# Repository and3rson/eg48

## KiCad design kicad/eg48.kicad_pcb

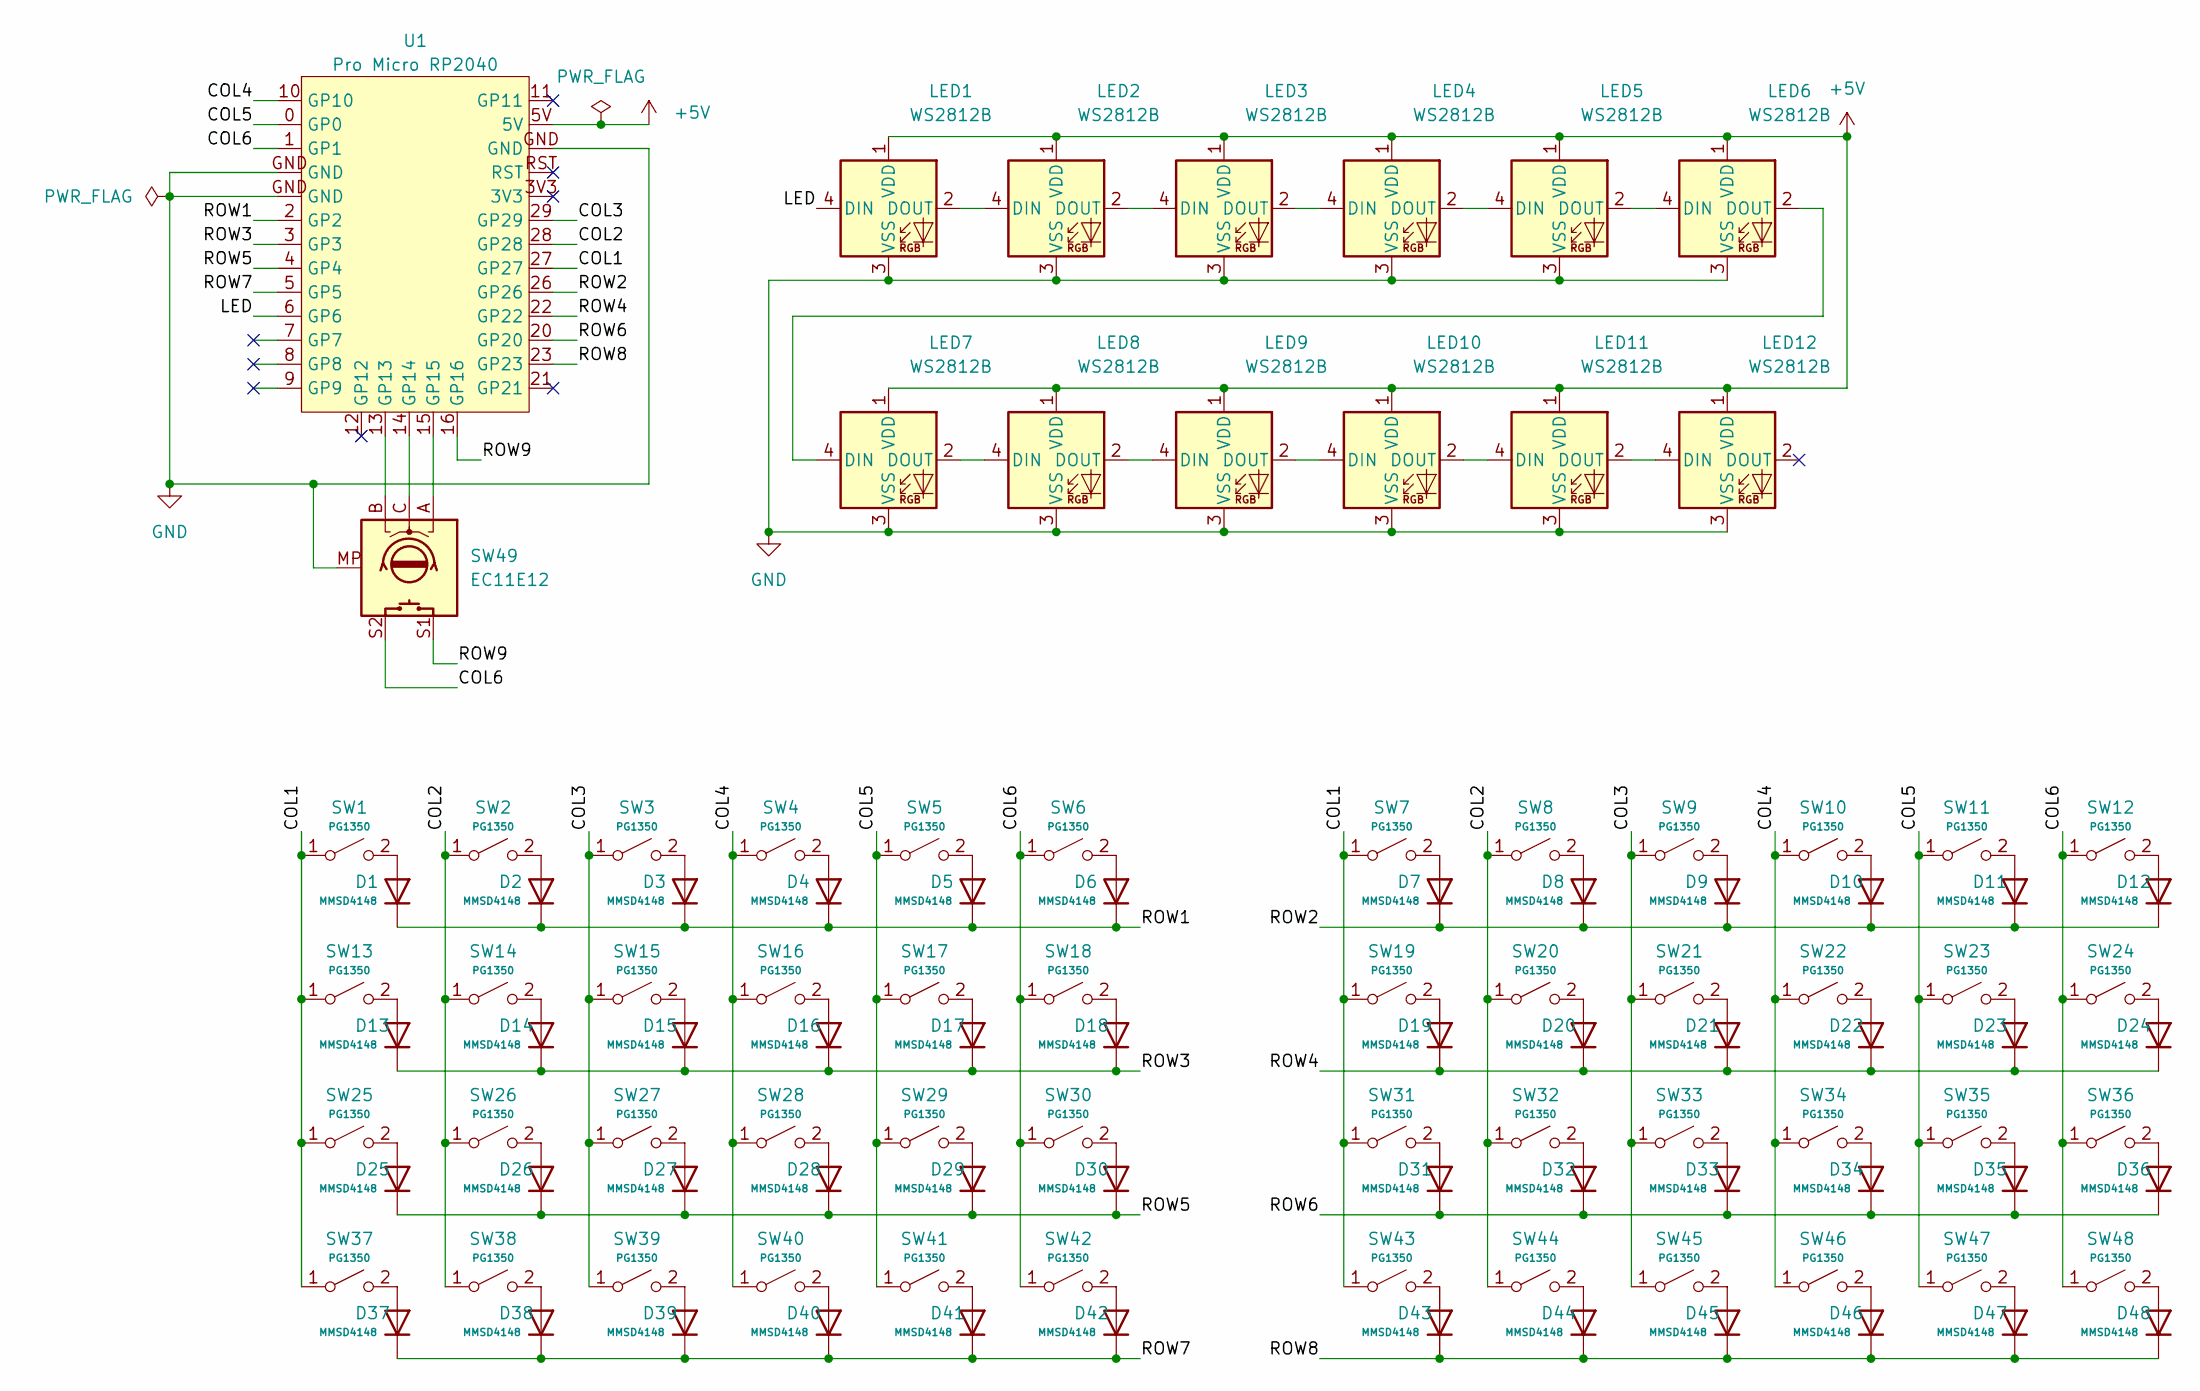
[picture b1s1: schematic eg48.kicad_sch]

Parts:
D1, D2, D3, D4, D5, D6, D7, D8, D9, D10, D11, D12, D13, D14, D15, D16, D17, D18, D19, D20, D21, D22, D23, D24, D25, D26, D27, D28, D29, D30, D31, D32, D33, D34, D35, D36, D37, D38, D39, D40, D41, D42, D43, D44, D45, D46, D47, D48: MMSD4148; D_SOD-123
LED1, LED2, LED3, LED4, LED5, LED6, LED7, LED8, LED9, LED10, LED11, LED12: WS2812B; LED_WS2812B_PLCC4_5.0x5.0mm_P3.2mm
SW1, SW2, SW3, SW4, SW5, SW6, SW7, SW8, SW9, SW10, SW11, SW12, SW13, SW14, SW15, SW16, SW17, SW18, SW19, SW20, SW21, SW22, SW23, SW24, SW25, SW26, SW27, SW28, SW29, SW30, SW31, SW32, SW33, SW34, SW35, SW36, SW37, SW38, SW39, SW40, SW41, SW42, SW43, SW44, SW45, SW46, SW47, SW48: PG1350; SW_PG1350
SW49: EC11E12; RotaryEncoder_Alps_EC11E-Switch_Vertical_H20mm
U1: Pro Micro RP2040; pro_micro_rp2040_min

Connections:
+5V: LED1.1 (VDD), LED2.1 (VDD), LED3.1 (VDD), LED4.1 (VDD), LED5.1 (VDD), LED6.1 (VDD), LED7.1 (VDD), LED8.1 (VDD), LED9.1 (VDD), LED10.1 (VDD), LED11.1 (VDD), LED12.1 (VDD), U1.5V
/COL1: SW1.1 (A), SW7.1 (A), SW13.1 (A), SW19.1 (A), SW25.1 (A), SW31.1 (A), SW37.1 (A), SW43.1 (A), U1.27 (GP27)
/COL2: SW2.1 (A), SW8.1 (A), SW14.1 (A), SW20.1 (A), SW26.1 (A), SW32.1 (A), SW38.1 (A), SW44.1 (A), U1.28 (GP28)
/COL3: SW3.1 (A), SW9.1 (A), SW15.1 (A), SW21.1 (A), SW27.1 (A), SW33.1 (A), SW39.1 (A), SW45.1 (A), U1.29 (GP29)
/COL4: SW4.1 (A), SW10.1 (A), SW16.1 (A), SW22.1 (A), SW28.1 (A), SW34.1 (A), SW40.1 (A), SW46.1 (A), U1.10 (GP10)
/COL5: SW5.1 (A), SW11.1 (A), SW17.1 (A), SW23.1 (A), SW29.1 (A), SW35.1 (A), SW41.1 (A), SW47.1 (A), U1.0 (GP0)
/COL6: SW6.1 (A), SW12.1 (A), SW18.1 (A), SW24.1 (A), SW30.1 (A), SW36.1 (A), SW42.1 (A), SW48.1 (A), SW49.S2, U1.1 (GP1)
/LED: LED1.4 (DIN), U1.6 (GP6)
/ROW1: D1.1 (K), D2.1 (K), D3.1 (K), D4.1 (K), D5.1 (K), D6.1 (K), U1.2 (GP2)
/ROW2: D7.1 (K), D8.1 (K), D9.1 (K), D10.1 (K), D11.1 (K), D12.1 (K), U1.26 (GP26)
/ROW3: D13.1 (K), D14.1 (K), D15.1 (K), D16.1 (K), D17.1 (K), D18.1 (K), U1.3 (GP3)
/ROW4: D19.1 (K), D20.1 (K), D21.1 (K), D22.1 (K), D23.1 (K), D24.1 (K), U1.22 (GP22)
/ROW5: D25.1 (K), D26.1 (K), D27.1 (K), D28.1 (K), D29.1 (K), D30.1 (K), U1.4 (GP4)
/ROW6: D31.1 (K), D32.1 (K), D33.1 (K), D34.1 (K), D35.1 (K), D36.1 (K), U1.20 (GP20)
/ROW7: D37.1 (K), D38.1 (K), D39.1 (K), D40.1 (K), D41.1 (K), D42.1 (K), U1.5 (GP5)
/ROW8: D43.1 (K), D44.1 (K), D45.1 (K), D46.1 (K), D47.1 (K), D48.1 (K), U1.23 (GP23)
/ROW9: SW49.S1, U1.16 (GP16)
GND: LED1.3 (VSS), LED2.3 (VSS), LED3.3 (VSS), LED4.3 (VSS), LED5.3 (VSS), LED6.3 (VSS), LED7.3 (VSS), LED8.3 (VSS), LED9.3 (VSS), LED10.3 (VSS), LED11.3 (VSS), LED12.3 (VSS), SW49.MP, U1.GND
unnamed: D1.2 (A), SW1.2 (B)
unnamed: D2.2 (A), SW2.2 (B)
unnamed: D3.2 (A), SW3.2 (B)
unnamed: D4.2 (A), SW4.2 (B)
unnamed: D5.2 (A), SW5.2 (B)
unnamed: D6.2 (A), SW6.2 (B)
unnamed: D7.2 (A), SW7.2 (B)
unnamed: D8.2 (A), SW8.2 (B)
unnamed: D9.2 (A), SW9.2 (B)
unnamed: D10.2 (A), SW10.2 (B)
unnamed: D11.2 (A), SW11.2 (B)
unnamed: D12.2 (A), SW12.2 (B)
unnamed: D13.2 (A), SW13.2 (B)
unnamed: D14.2 (A), SW14.2 (B)
unnamed: D15.2 (A), SW15.2 (B)
unnamed: D16.2 (A), SW16.2 (B)
unnamed: D17.2 (A), SW17.2 (B)
unnamed: D18.2 (A), SW18.2 (B)
unnamed: D19.2 (A), SW19.2 (B)
unnamed: D20.2 (A), SW20.2 (B)
unnamed: D21.2 (A), SW21.2 (B)
unnamed: D22.2 (A), SW22.2 (B)
unnamed: D23.2 (A), SW23.2 (B)
unnamed: D24.2 (A), SW24.2 (B)
unnamed: D25.2 (A), SW25.2 (B)
unnamed: D26.2 (A), SW26.2 (B)
unnamed: D27.2 (A), SW27.2 (B)
unnamed: D28.2 (A), SW28.2 (B)
unnamed: D29.2 (A), SW29.2 (B)
unnamed: D30.2 (A), SW30.2 (B)
unnamed: D31.2 (A), SW31.2 (B)
unnamed: D32.2 (A), SW32.2 (B)
unnamed: D33.2 (A), SW33.2 (B)
unnamed: D34.2 (A), SW34.2 (B)
unnamed: D35.2 (A), SW35.2 (B)
unnamed: D36.2 (A), SW36.2 (B)
unnamed: D37.2 (A), SW37.2 (B)
unnamed: D38.2 (A), SW38.2 (B)
unnamed: D39.2 (A), SW39.2 (B)
unnamed: D40.2 (A), SW40.2 (B)
unnamed: D41.2 (A), SW41.2 (B)
unnamed: D42.2 (A), SW42.2 (B)
unnamed: D43.2 (A), SW43.2 (B)
unnamed: D44.2 (A), SW44.2 (B)
unnamed: D45.2 (A), SW45.2 (B)
unnamed: D46.2 (A), SW46.2 (B)
unnamed: D47.2 (A), SW47.2 (B)
unnamed: D48.2 (A), SW48.2 (B)
unnamed: LED1.2 (DOUT), LED2.4 (DIN)
unnamed: LED2.2 (DOUT), LED3.4 (DIN)
unnamed: LED3.2 (DOUT), LED4.4 (DIN)
unnamed: LED4.2 (DOUT), LED5.4 (DIN)
unnamed: LED5.2 (DOUT), LED6.4 (DIN)
unnamed: LED6.2 (DOUT), LED7.4 (DIN)
unnamed: LED7.2 (DOUT), LED8.4 (DIN)
unnamed: LED8.2 (DOUT), LED9.4 (DIN)
unnamed: LED9.2 (DOUT), LED10.4 (DIN)
unnamed: LED10.2 (DOUT), LED11.4 (DIN)
unnamed: LED11.2 (DOUT), LED12.4 (DIN)
unnamed: SW49.B, U1.13 (GP13)
unnamed: SW49.C, U1.14 (GP14)
unnamed: SW49.A, U1.15 (GP15)

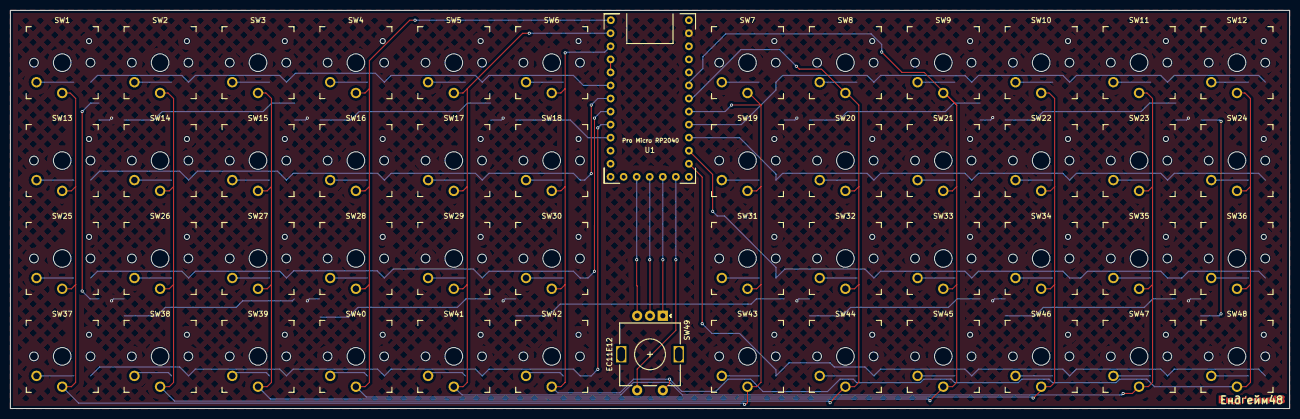
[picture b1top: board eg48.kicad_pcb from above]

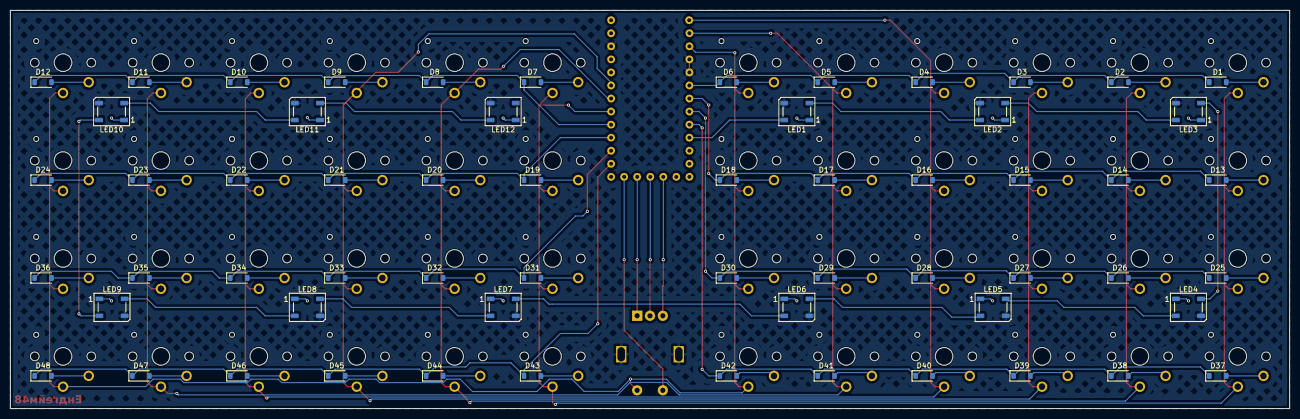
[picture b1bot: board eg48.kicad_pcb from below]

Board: 2 copper layers, 248.9 x 77.5 mm, 110 parts (60 on the bottom side), 80 nets.

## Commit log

2025-01-01 Initial schematics
2025-01-01 Update kicad files, add 3D models
2025-06-25 Kicad 9, nicer routing, clearance for rp2040
2025-06-25 Titles
2025-09-07 V1 gerbers
2025-10-01 Make diodes more obvious, make text nicer
2025-10-10 Add docs stub
2025-10-10 Add back docs
2025-10-14 Unrounded
2025-10-14 Final?
2025-10-16 Reroute to avoid using bottom pins
2025-10-16 Remove 5 bottom pins
2025-10-16 New plates
